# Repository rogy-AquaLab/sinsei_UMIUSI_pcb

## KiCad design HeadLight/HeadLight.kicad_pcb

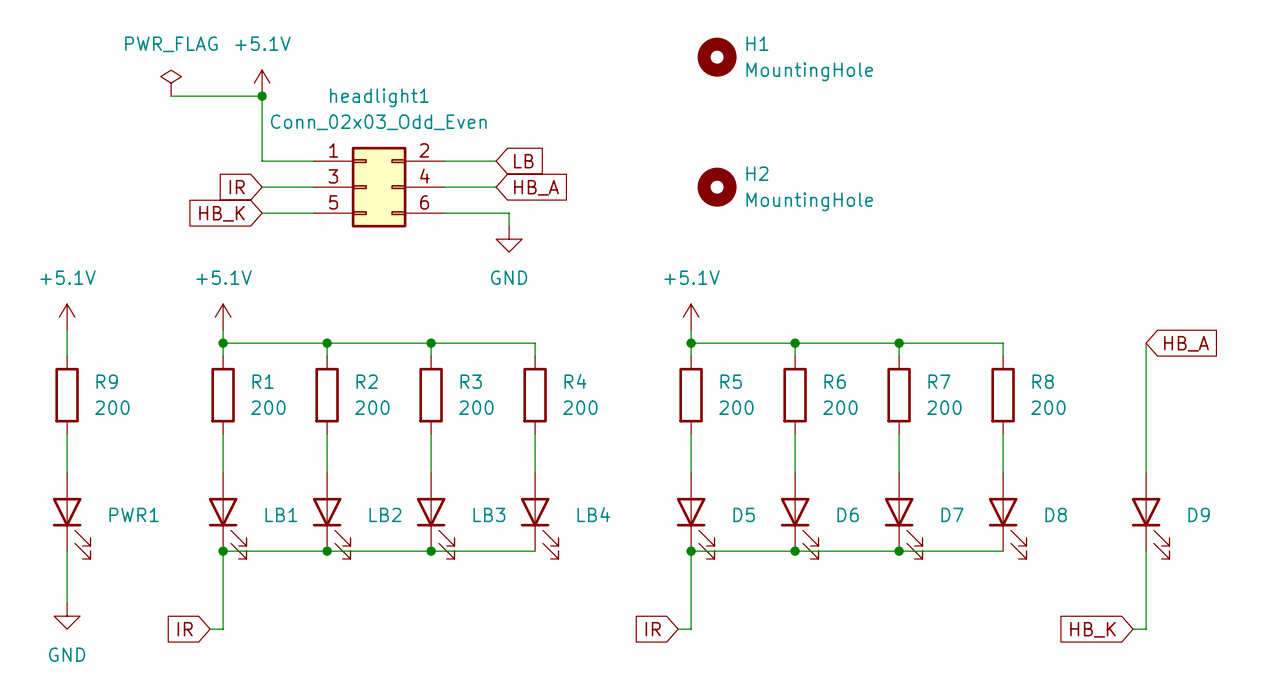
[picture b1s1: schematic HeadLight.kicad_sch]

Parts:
D5: IR1; LED_1206_3216Metric_Pad1.42x1.75mm_HandSolder
D6, D7, D8: LED; LED_1206_3216Metric_Pad1.42x1.75mm_HandSolder
D9: LED; power led
H1, H2: MountingHole; MountingHole_3.2mm_M3
LB1, LB2, LB3, LB4: LED_1206_3216Metric_Pad1.42x1.75mm_HandSolder
PWR1: LED; LED_1206_3216Metric_Pad1.42x1.75mm_HandSolder
R1, R2, R3, R4, R5, R6, R7, R8, R9: 200; R_0603_1608Metric_Pad0.98x0.95mm_HandSolder
headlight1: Conn_02x03_Odd_Even; PinHeader_2x03_P2.54mm_Vertical

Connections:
+5.1V: R1.1, R2.1, R3.1, R4.1, R5.1, R6.1, R7.1, R8.1, R9.1, headlight1.1
GND: PWR1.1 (K), headlight1.6
HB_A: D9.2 (A), headlight1.4
HB_K: D9.1 (K), headlight1.5
IR: D5.1 (K), D6.1 (K), D7.1 (K), D8.1 (K), LB1.1 (K), LB2.1 (K), LB3.1 (K), LB4.1 (K), headlight1.3
LB: headlight1.2
unnamed: D5.2 (A), R5.2
unnamed: D6.2 (A), R6.2
unnamed: D7.2 (A), R7.2
unnamed: D8.2 (A), R8.2
unnamed: LB1.2 (A), R1.2
unnamed: LB2.2 (A), R2.2
unnamed: LB3.2 (A), R3.2
unnamed: LB4.2 (A), R4.2
unnamed: PWR1.2 (A), R9.2

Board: 2 copper layers, 22 parts (0 on the bottom side), 14 nets, no tracks yet.

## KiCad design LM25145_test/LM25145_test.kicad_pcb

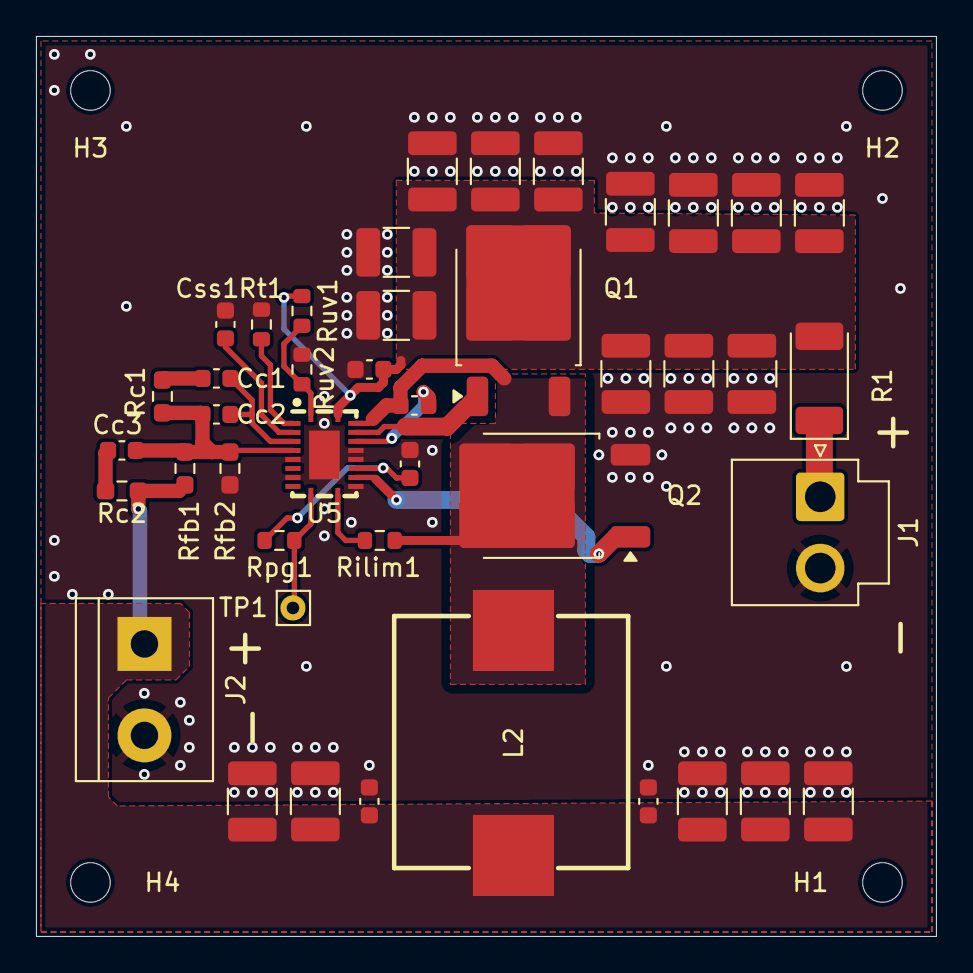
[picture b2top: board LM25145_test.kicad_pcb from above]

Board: 2 copper layers, 50.0 x 50.0 mm, 47 parts (0 on the bottom side), 18 nets.

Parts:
Cbst1: 0.1u; C_0603_1608Metric
Cc1: 5.6n; C_0603_1608Metric
Cc2: 82p; C_0603_1608Metric
Cc3: 1500p; C_0603_1608Metric
Cin1, Cin2, Cin3, Cin4, Cin5, Cin6, Cin7, Cin8, Cin9, Cin10, Cin11, Cin12: 10u; C_1210_3225Metric_Pad1.33x2.70mm_HandSolder
Cout1: 100p; C_0603_1608Metric
Cout2: 0.1u; C_0603_1608Metric
Cout3: 10u; C_1210_3225Metric_Pad1.33x2.70mm_HandSolder
Cout4, Cout5, Cout6, Cout7: 47u; C_1210_3225Metric_Pad1.33x2.70mm_HandSolder
Css1: 0.1u; C_0603_1608Metric
Cvcc1: 2.2u; C_0603_1608Metric
Cvin1: 0.1u; C_0603_1608Metric
H1, H2, H3, H4: MountingHole; MountingHole_2.2mm_M2
J1: Conn_01x02_Socket; JST_VH_B2P-VH_1x02_P3.96mm_Vertical
J2: Conn_01x02_Socket; TerminalBlock_bornier-2_P5.08mm
L2: 10u; IND-SMD_L13.8-W12.6
Q1, Q2: TO-252-2
R1: 20m; D_2010_5025Metric_Pad1.52x2.65mm_HandSolder
Rc1: 10k; R_0603_1608Metric_Pad0.98x0.95mm_HandSolder
Rc2: 560; R_0603_1608Metric_Pad0.98x0.95mm_HandSolder
Rfb1: 18k; R_0603_1608Metric_Pad0.98x0.95mm_HandSolder
Rfb2: 3.3k; R_0603_1608Metric_Pad0.98x0.95mm_HandSolder
Rilim1: 180; R_0603_1608Metric
Rpg1: 51k; R_0603_1608Metric
Rt1: 33k; R_0603_1608Metric
Ruv1: 75k; R_0603_1608Metric
Ruv2: 12k; R_0603_1608Metric
TP1: TestPoint; Pin_D0.7mm_L6.5mm_W1.8mm_FlatFork
U5: VQFN-20_L4.5-W3.5-P0.50-BL-EP

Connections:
+5.1V: Cout1.2, Cout2.2, Cout3.1, Cout4.1, Cout5.1, Cout6.1, Cout7.1, J2.1, L2.2, Rc2.2, Rfb1.2
+7.5V: Cvcc1.1, Rpg1.2, U5.14 (VCC)
+24V: Cin1.1, Cin2.1, Cin3.1, Cin4.1, Cin5.1, Cin6.1, Cin7.1, Cin8.1, Cin9.1, Cin10.1, Cin11.1, Cin12.1, Cvin1.1, Q1.2 (D), R1.2, Ruv1.1, U5.20 (VIN)
GND: Cin1.2, Cin2.2, Cin3.2, Cin4.2, Cin5.2, Cin6.2, Cin7.2, Cin8.2, Cin9.2, Cin10.2, Cin11.2, Cin12.2, Cout1.1, Cout2.1, Cout3.2, Cout4.2, Cout5.2, Cout6.2, Cout7.2, Css1.1, Cvcc1.2, Cvin1.2, J1.2, J2.2, Q2.3 (S), Rfb2.1, Rt1.1, Ruv2.2, U5.6 (AGND), U5.8 (SYNCIN), U5.12 (PGND), U5.15 (EP), U5.16 (NC), U5.21 (EP)
unnamed: Cc1.1, Rc1.1
unnamed: Cc3.1, Rc2.1
unnamed: J1.1, R1.1
unnamed: Q1.1 (G), U5.18 (HO)
unnamed: Cbst1.2, L2.1, Q1.3 (S), Q2.2 (D), Rilim1.2, U5.19 (SW)
unnamed: Q2.1 (G), U5.13 (LO)
unnamed: Cbst1.1, U5.17 (BST)
unnamed: Cc1.2, Cc2.2, U5.4 (COMP)
unnamed: Ruv1.2, Ruv2.1, U5.1 (EN/UVLO)
unnamed: Cc2.1, Cc3.2, Rc1.2, Rfb1.1, Rfb2.2, U5.5 (FB)
unnamed: Rilim1.1, U5.11 (ILIM)
unnamed: Rt1.2, U5.2 (RT)
unnamed: Css1.2, U5.3 (SS/TRK)
PGOOD: Rpg1.1, TP1.1, U5.10 (PGOOD)

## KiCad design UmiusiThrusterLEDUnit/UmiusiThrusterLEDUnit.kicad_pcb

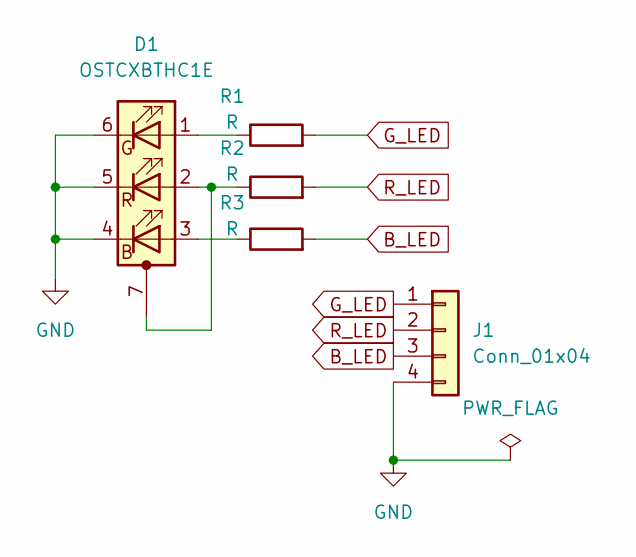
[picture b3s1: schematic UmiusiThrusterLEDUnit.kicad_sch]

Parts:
D1: OSTCXBTHC1E
J1: Conn_01x04; PinHeader_1x04_P2.54mm_Vertical
R1, R2, R3: R; R_Axial_DIN0207_L6.3mm_D2.5mm_P7.62mm_Horizontal

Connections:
B_LED: J1.3, R3.2
GND: D1.4 (BK), D1.5 (RK), D1.6 (GK), J1.4
G_LED: J1.1, R1.2
unnamed: D1.3 (BA), R3.1
unnamed: D1.1 (GA), R1.1
unnamed: D1.2 (RA), D1.7 (PAD), R2.1
R_LED: J1.2, R2.2

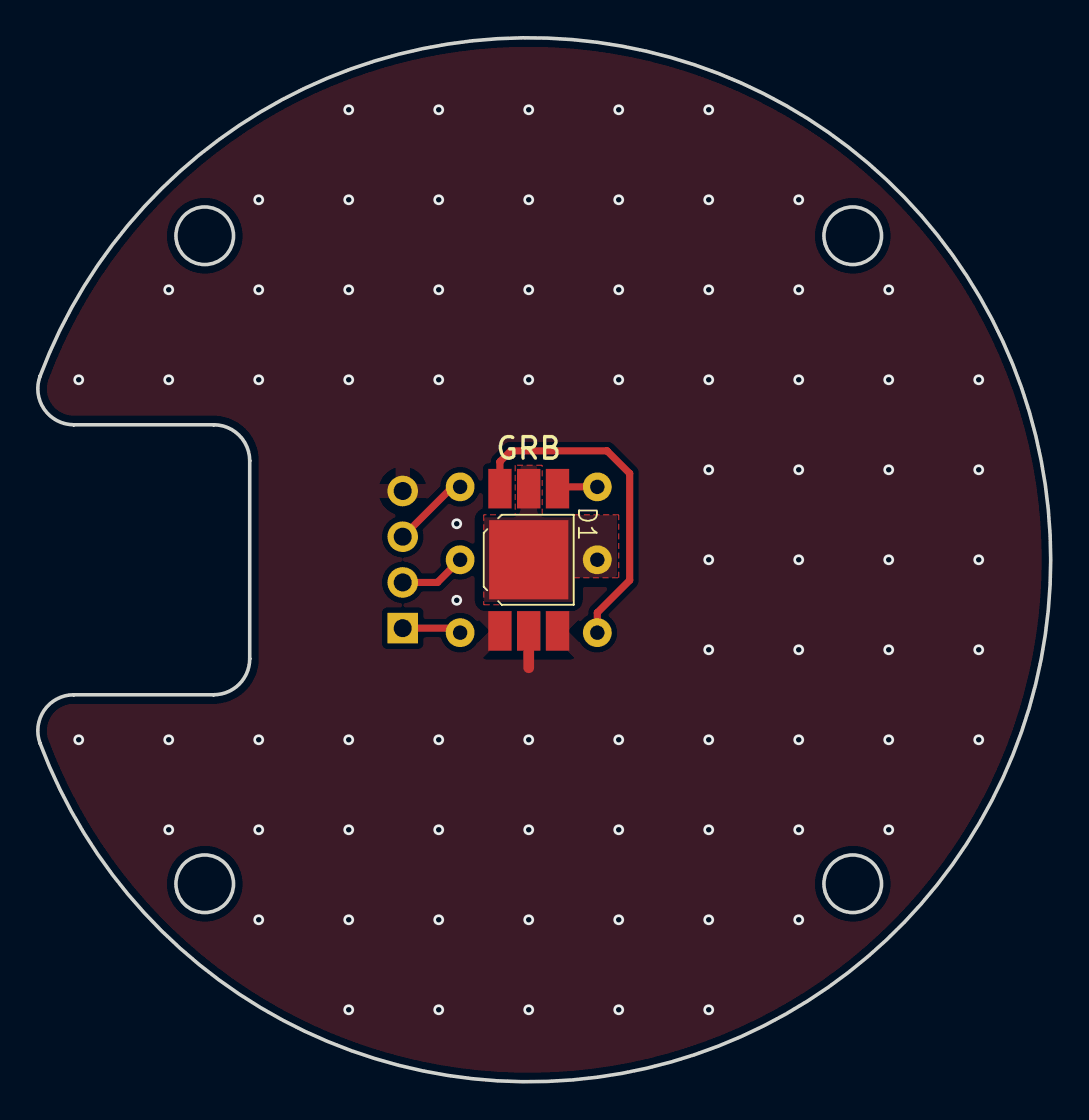
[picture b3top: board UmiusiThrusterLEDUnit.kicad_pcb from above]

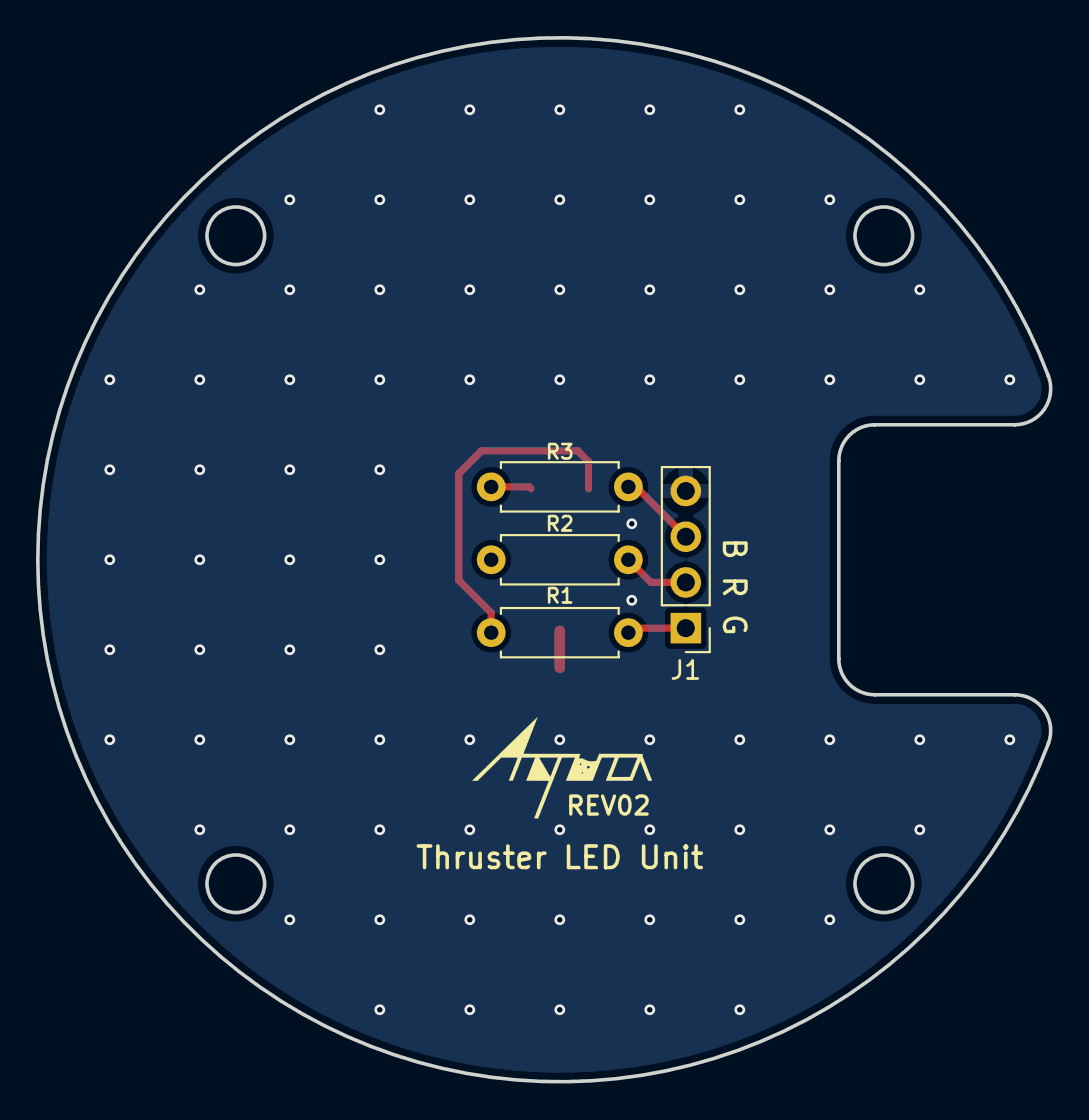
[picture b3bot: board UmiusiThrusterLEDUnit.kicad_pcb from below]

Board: 2 copper layers, 56.3 x 58.0 mm, 5 parts (4 on the bottom side), 7 nets.

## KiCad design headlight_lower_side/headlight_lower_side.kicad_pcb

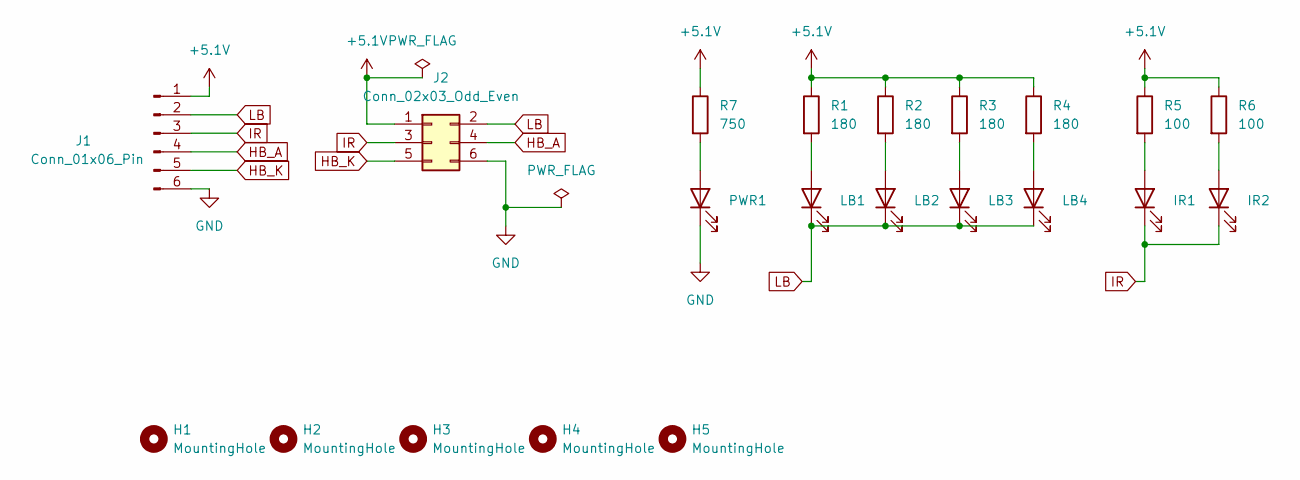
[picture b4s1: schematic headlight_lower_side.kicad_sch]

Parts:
H1, H2, H3, H4, H5: MountingHole; MountingHole_3.2mm_M3
IR1, IR2: LED_D3.0mm_Horizontal_O3.81mm_Z2.0mm
J1: Conn_01x06_Pin; JST_XA_B06B-XASK-1_1x06_P2.50mm_Vertical
J2: Conn_02x03_Odd_Even; PinHeader_2x03_P2.54mm_Horizontal
LB1, LB2, LB3, LB4: white; LED_0805_2012Metric_Pad1.15x1.40mm_HandSolder
PWR1: white; LED_0805_2012Metric_Pad1.15x1.40mm_HandSolder
R1, R2, R3, R4: 180; R_Axial_DIN0207_L6.3mm_D2.5mm_P10.16mm_Horizontal
R5, R6: 100; R_Axial_DIN0207_L6.3mm_D2.5mm_P10.16mm_Horizontal
R7: 750; R_Axial_DIN0207_L6.3mm_D2.5mm_P10.16mm_Horizontal

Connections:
+5.1V: J1.1, J2.1, R1.1, R2.1, R3.1, R4.1, R5.1, R6.1, R7.1
GND: J1.6, J2.6, PWR1.1 (K)
HB_A: J1.4, J2.4
HB_K: J1.5, J2.5
IR: IR1.1 (K), IR2.1 (K), J1.3, J2.3
LB: J1.2, J2.2, LB1.1 (K), LB2.1 (K), LB3.1 (K), LB4.1 (K)
unnamed: IR1.2 (A), R5.2
unnamed: IR2.2 (A), R6.2
unnamed: LB1.2 (A), R1.2
unnamed: LB2.2 (A), R2.2
unnamed: LB3.2 (A), R3.2
unnamed: LB4.2 (A), R4.2
unnamed: PWR1.2 (A), R7.2

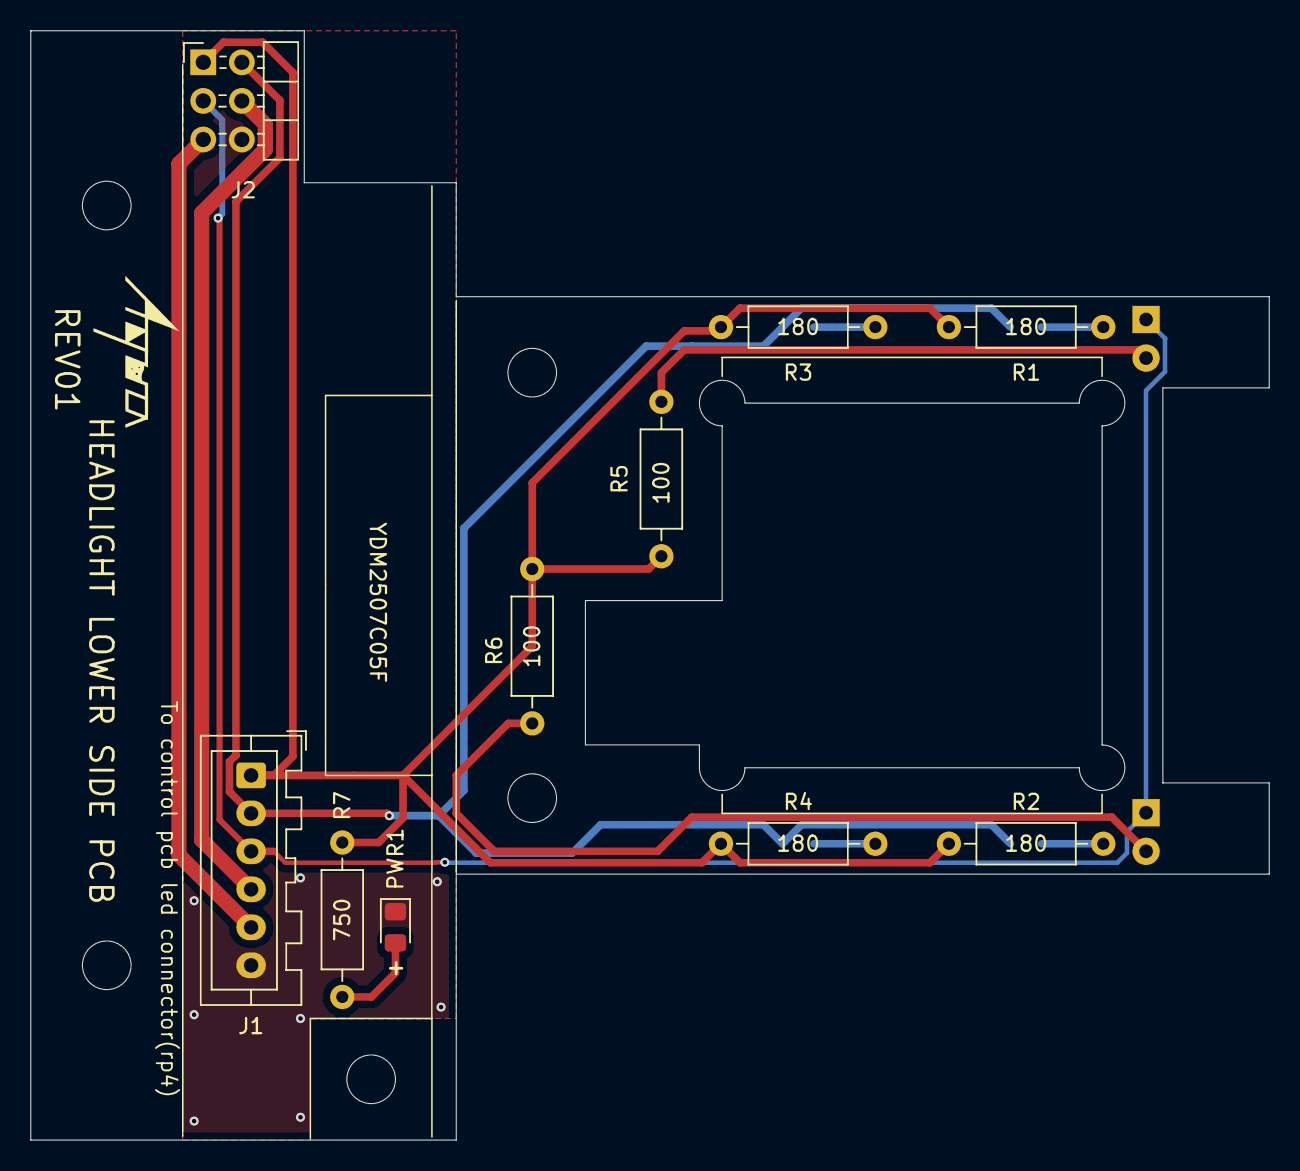
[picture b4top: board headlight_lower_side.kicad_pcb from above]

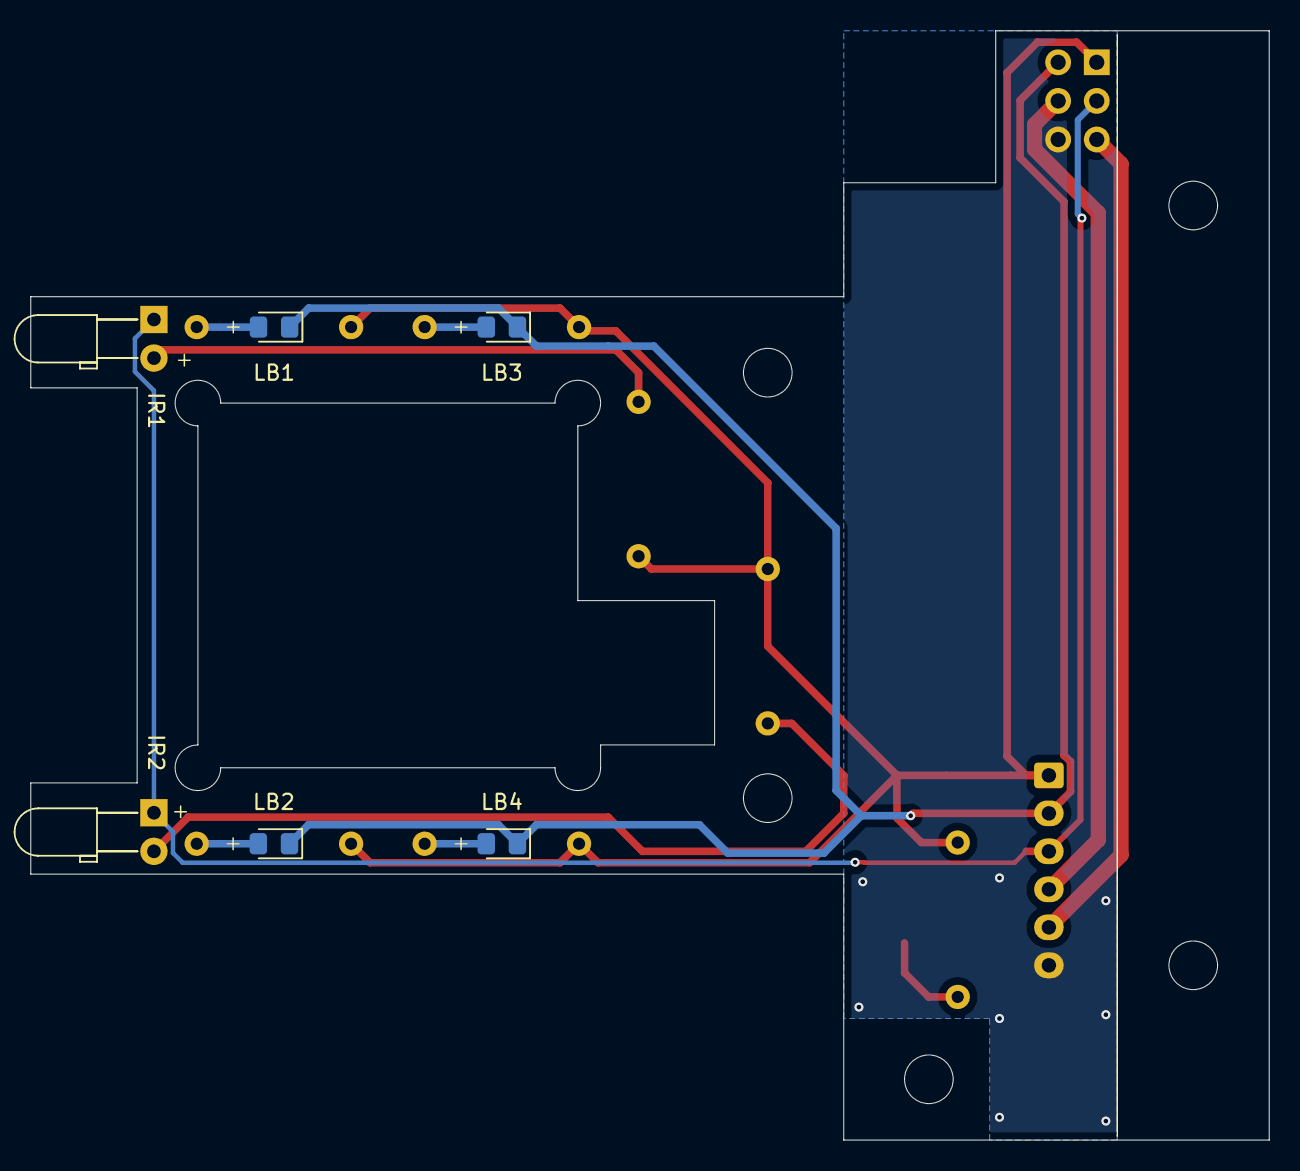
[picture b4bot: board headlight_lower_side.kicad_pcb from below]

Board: 2 copper layers, 81.5 x 73.0 mm, 21 parts (6 on the bottom side), 13 nets.

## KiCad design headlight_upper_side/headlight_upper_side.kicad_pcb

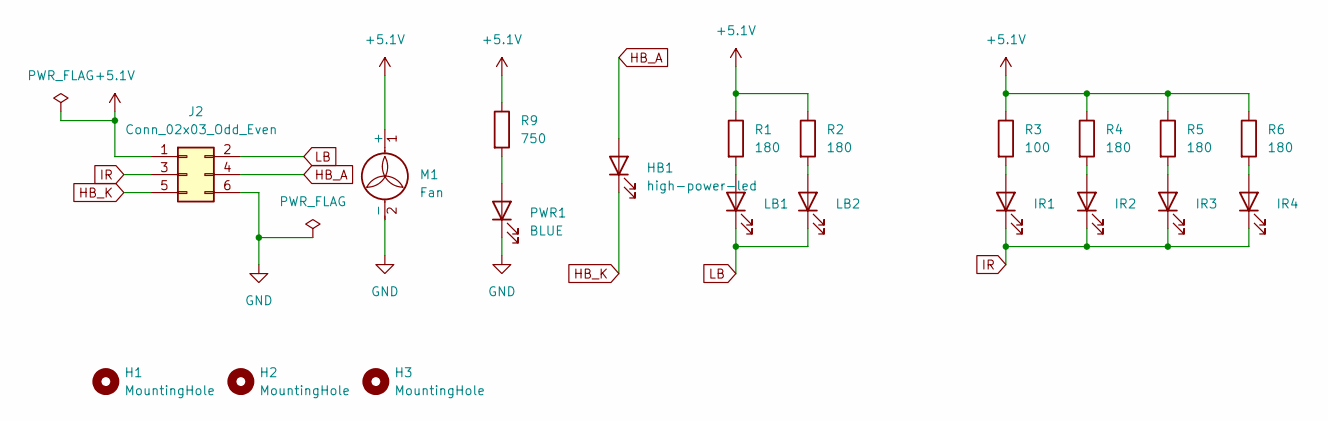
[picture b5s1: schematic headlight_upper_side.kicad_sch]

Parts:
H1, H2, H3: MountingHole; MountingHole_3.2mm_M3
HB1: high-power-led; power led
IR1, IR2, IR3, IR4: LED_D5.0mm
J2: Conn_02x03_Odd_Even; PinSocket_2x03_P2.54mm_Vertical
LB1, LB2: LED_D5.0mm
M1: Fan; PinHeader_1x02_P2.54mm_Vertical
PWR1: BLUE; LED_0805_2012Metric_Pad1.15x1.40mm_HandSolder
R1, R2, R4, R5, R6: 180; R_Axial_DIN0207_L6.3mm_D2.5mm_P10.16mm_Horizontal
R3: 100; R_Axial_DIN0207_L6.3mm_D2.5mm_P10.16mm_Horizontal
R9: 750; R_Axial_DIN0207_L6.3mm_D2.5mm_P10.16mm_Horizontal

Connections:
+5.1V: J2.1, M1.1 (+), R1.1, R2.1, R3.1, R4.1, R5.1, R6.1, R9.1
GND: J2.6, M1.2 (-), PWR1.1 (K)
HB_A: HB1.2 (A), J2.4
HB_K: HB1.1 (K), J2.5
IR: IR1.1 (K), IR2.1 (K), IR3.1 (K), IR4.1 (K), J2.3
LB: J2.2, LB1.1 (K), LB2.1 (K)
unnamed: IR1.2 (A), R3.2
unnamed: IR2.2 (A), R4.2
unnamed: IR3.2 (A), R5.2
unnamed: IR4.2 (A), R6.2
unnamed: LB1.2 (A), R1.2
unnamed: LB2.2 (A), R2.2
unnamed: PWR1.2 (A), R9.2

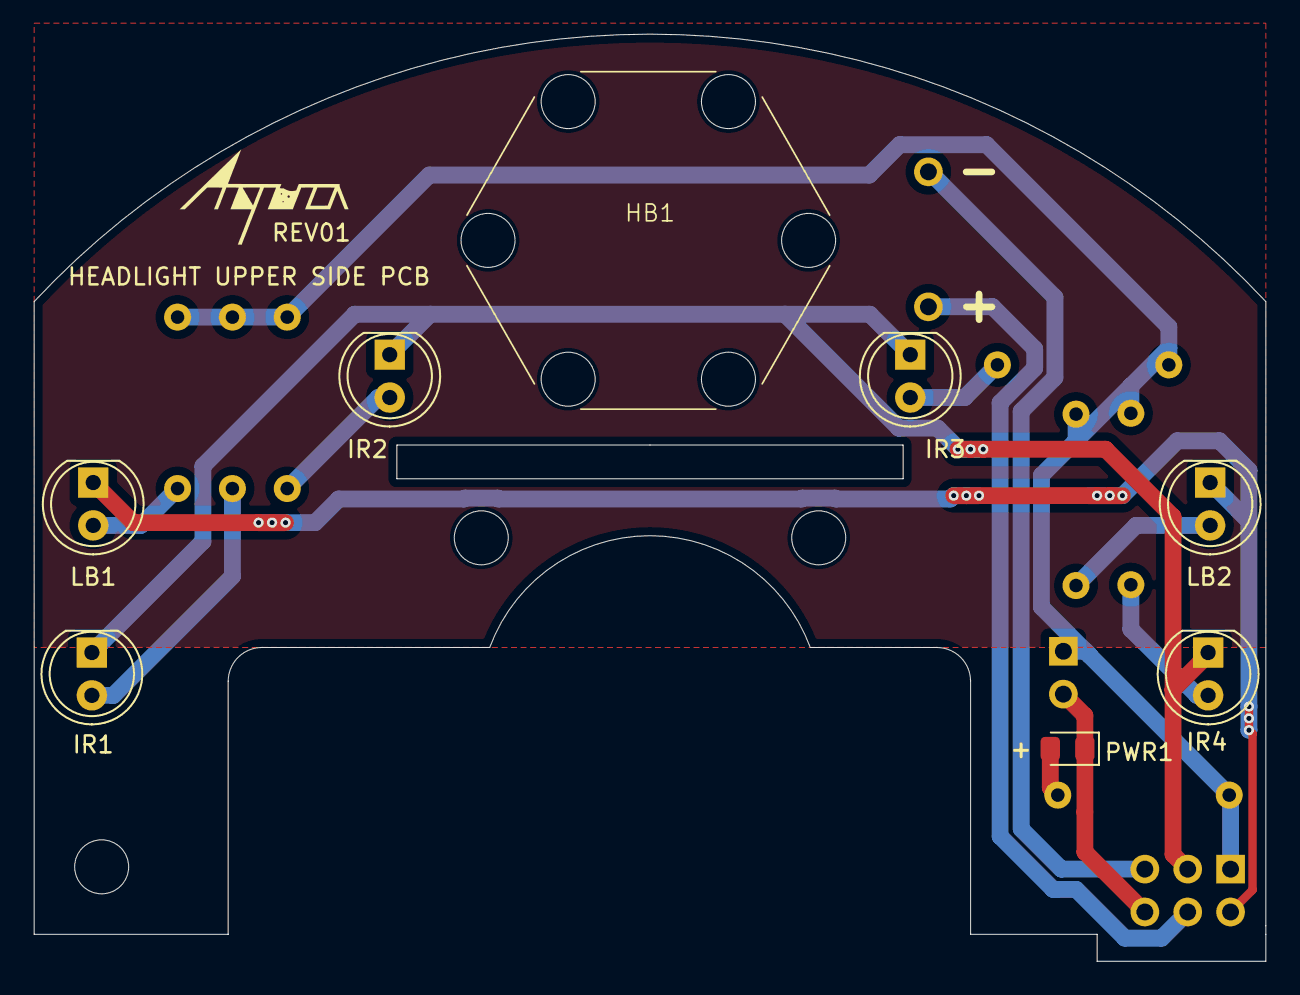
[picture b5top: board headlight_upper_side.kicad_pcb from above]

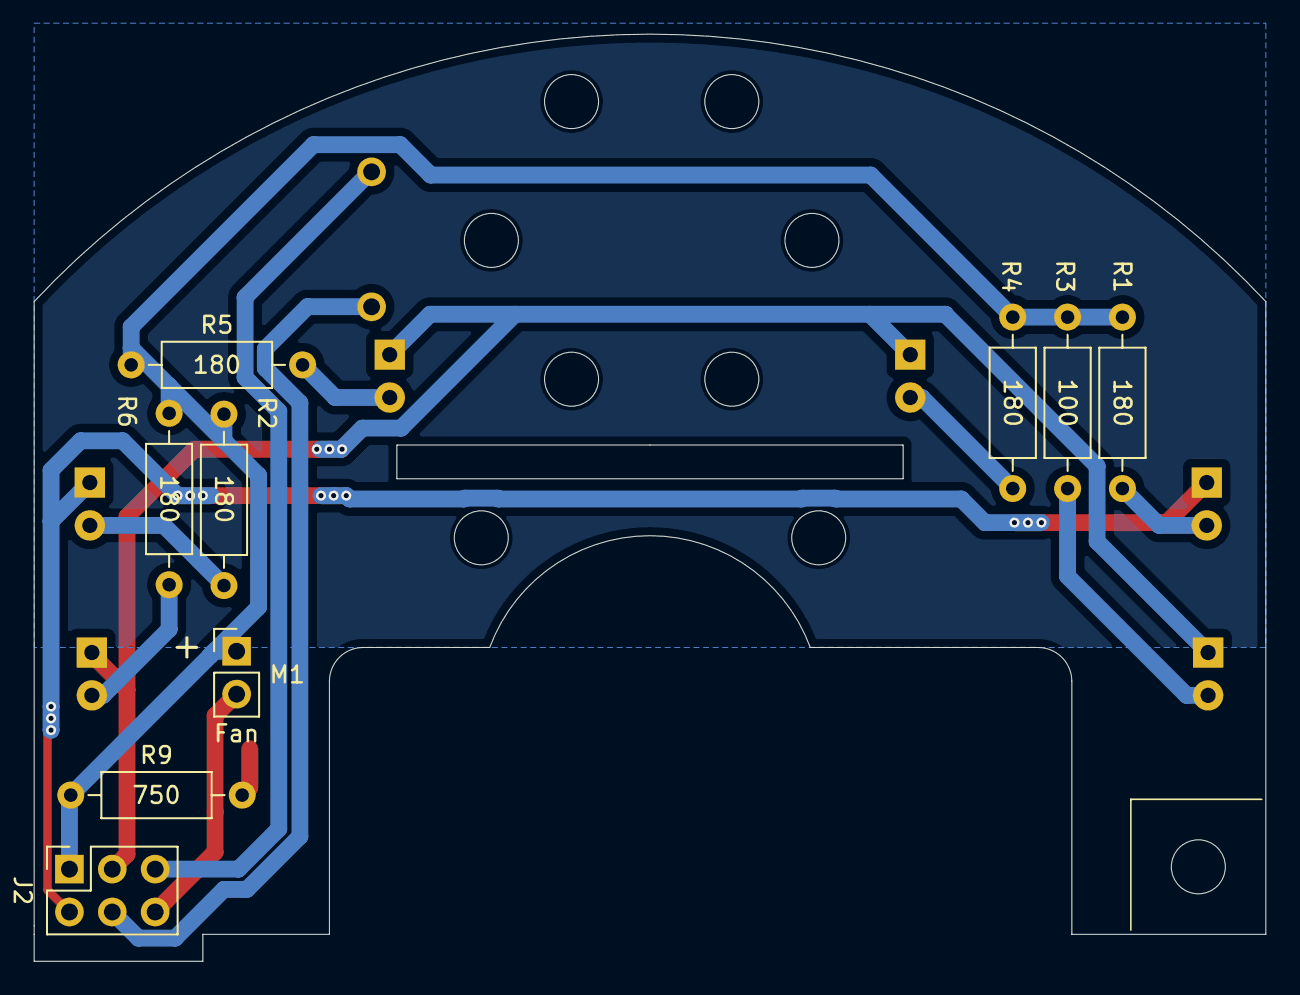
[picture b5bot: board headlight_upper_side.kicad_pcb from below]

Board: 2 copper layers, 73.0 x 55.0 mm, 20 parts (9 on the bottom side), 13 nets.

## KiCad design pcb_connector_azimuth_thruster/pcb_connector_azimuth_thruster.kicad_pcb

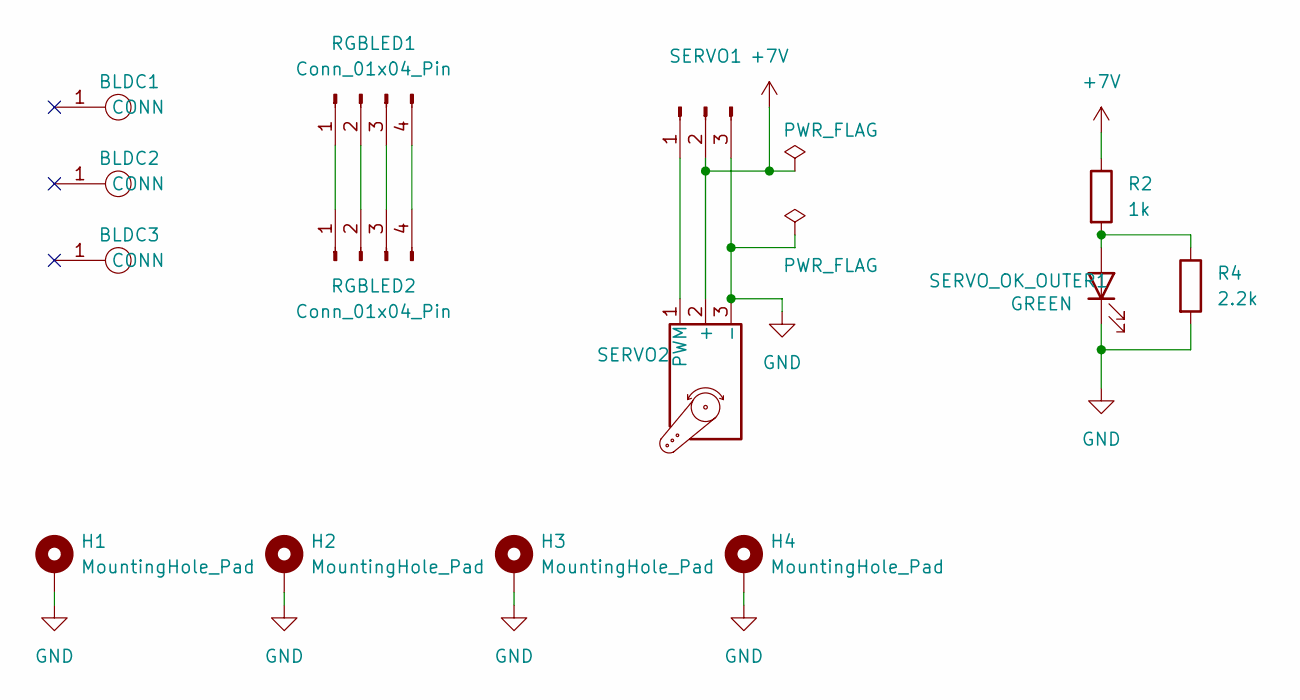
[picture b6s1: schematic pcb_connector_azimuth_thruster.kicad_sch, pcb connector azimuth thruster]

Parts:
BLDC1, BLDC2, BLDC3: bldc_connector
H1, H2, H3, H4: MountingHole_Pad; MountingHole_3.2mm_M3_large_PAD_for_spacer
R2: 1k; R_0603_1608Metric_Pad0.98x0.95mm_HandSolder
R4: 2.2k; R_0603_1608Metric_Pad0.98x0.95mm_HandSolder
RGBLED1: Conn_01x04_Pin; JST_XA_B04B-XASK-1_1x04_P2.50mm_Vertical
RGBLED2: Conn_01x04_Pin; PinHeader_1x04_P2.54mm_Vertical
SERVO1: JST_XA_B03B-XASK-1_1x03_P2.50mm_Vertical
SERVO2: PinHeader_1x03_P2.54mm_Vertical
SERVO_OK_OUTER1: GREEN; LED_0805_2012Metric_Pad1.15x1.40mm_HandSolder

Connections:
+7V: R2.1, SERVO1.2, SERVO2.2 (+)
GND: H1.1, H2.1, H3.1, H4.1, R4.2, SERVO1.3, SERVO2.3 (-), SERVO_OK_OUTER1.1 (K)
unnamed: RGBLED1.1, RGBLED2.1
unnamed: RGBLED1.2, RGBLED2.2
unnamed: RGBLED1.3, RGBLED2.3
unnamed: RGBLED1.4, RGBLED2.4
unnamed: SERVO1.1, SERVO2.1 (PWM)
unnamed: R2.2, R4.1, SERVO_OK_OUTER1.2 (A)

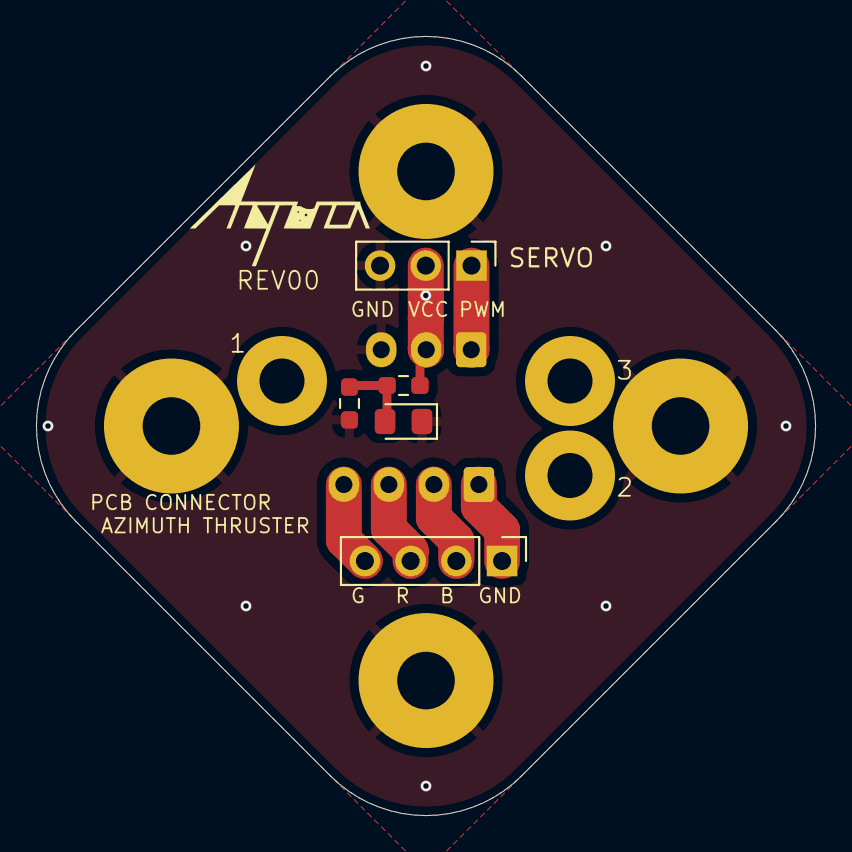
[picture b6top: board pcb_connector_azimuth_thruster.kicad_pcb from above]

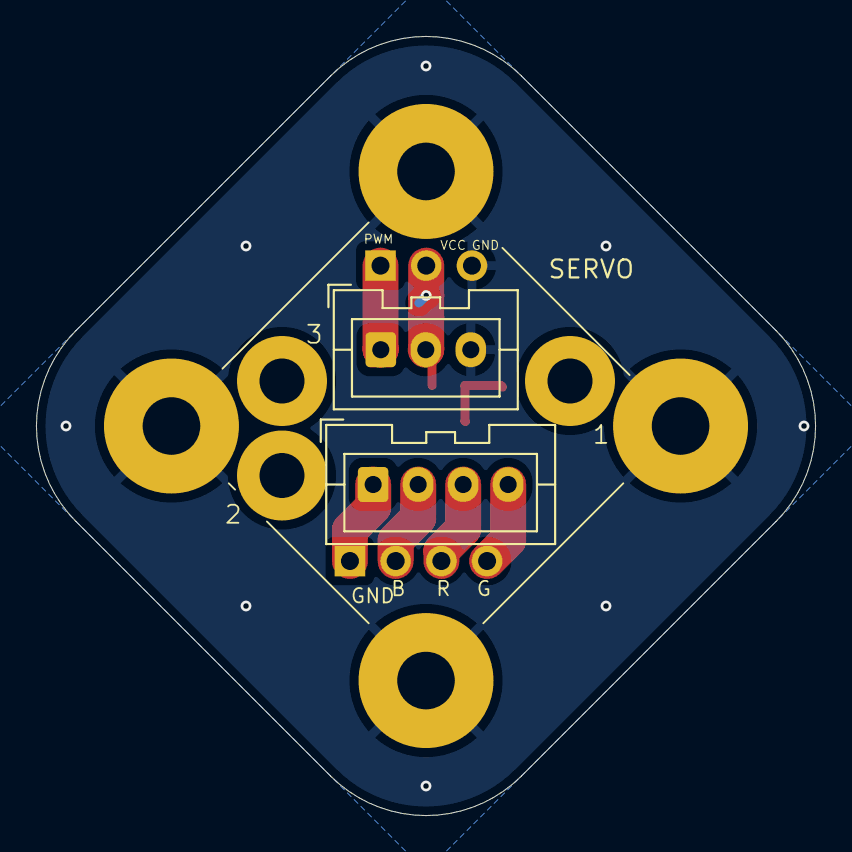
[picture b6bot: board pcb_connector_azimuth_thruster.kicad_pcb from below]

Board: 2 copper layers, 43.3 x 43.3 mm, 14 parts (2 on the bottom side), 8 nets.

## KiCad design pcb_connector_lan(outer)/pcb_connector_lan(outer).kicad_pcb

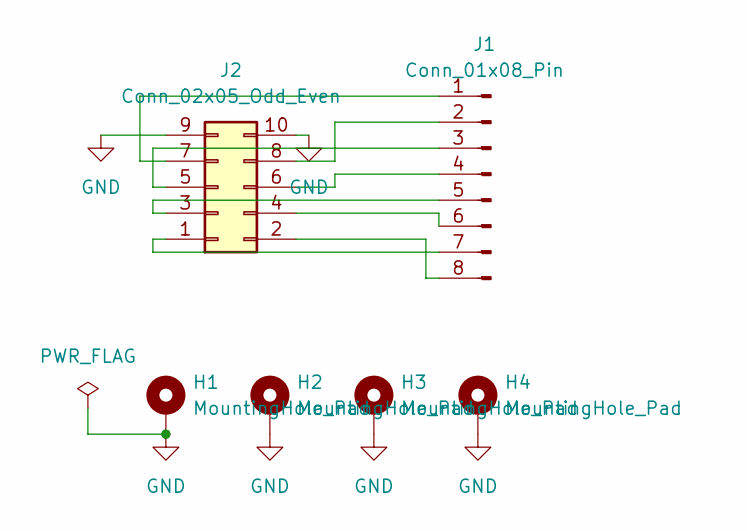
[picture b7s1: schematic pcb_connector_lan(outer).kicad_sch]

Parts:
H1, H2, H3, H4: MountingHole_Pad; MountingHole_3.2mm_M3_large_PAD_for_spacer
J1: Conn_01x08_Pin; PinSocket_1x08_P2.00mm_Vertical
J2: Conn_02x05_Odd_Even; PinSocket_2x05_P2.54mm_Vertical

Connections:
GND: H1.1, H2.1, H3.1, H4.1, J2.9, J2.10
unnamed: J1.1, J2.7
unnamed: J1.2, J2.8
unnamed: J1.3, J2.5
unnamed: J1.4, J2.6
unnamed: J1.5, J2.3
unnamed: J1.6, J2.4
unnamed: J1.7, J2.1
unnamed: J1.8, J2.2

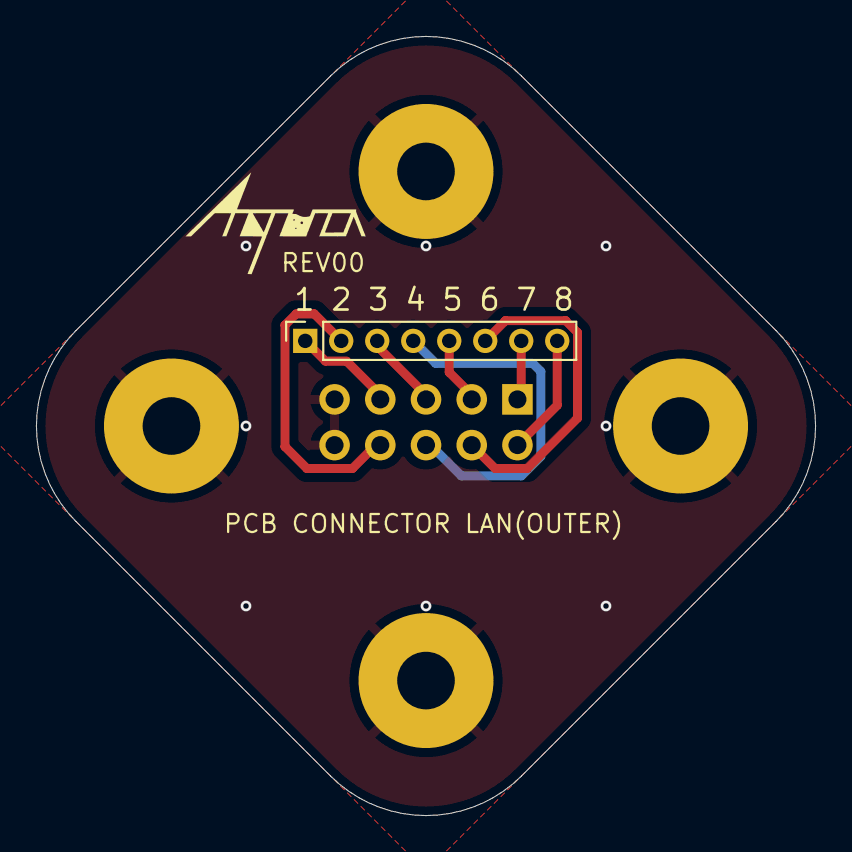
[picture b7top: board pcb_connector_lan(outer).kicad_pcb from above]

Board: 2 copper layers, 43.3 x 43.3 mm, 6 parts (1 on the bottom side), 9 nets.

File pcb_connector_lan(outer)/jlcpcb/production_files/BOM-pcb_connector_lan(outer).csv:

Comment,Designator,Footprint,LCSC,Quantity
Conn_01x08_Pin,J1,PinSocket_1x08_P2.00mm_Vertical,,1
Conn_02x05_Odd_Even,J2,PinSocket_2x05_P2.54mm_Vertical,,1
